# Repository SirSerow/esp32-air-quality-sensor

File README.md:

# ESP32 Air Quality Sensor

ESP32-C6 firmware for reading AHT20 (temperature/humidity) and ENS160 (air quality) data, storing historical samples (SD card preferred, NVS fallback), showing live values on an SSD1306 OLED, and serving a built-in web dashboard over external Wi-Fi when available, with SoftAP fallback.

## Sensor Readings

The device measures six quantities using two sensors on the I²C bus:

| Metric | Sensor | Unit | Good | Moderate | Poor |
|---|---|---|---|---|---|
| Temperature | AHT20 | °C | ≤ 26 | 26 – 30 | > 30 |
| Relative Humidity | AHT20 | % | 30 – 60 | 60 – 70 | > 70 or < 20 |
| eCO₂ | ENS160 | ppm | < 800 | 800 – 2 000 | > 2 000 |
| AQI | ENS160 | 1–5 | 1 – 2 | 3 | 4 – 5 |
| TVOC | ENS160 | ppb | < 220 | 220 – 660 | > 660 |
| ENS Validity | ENS160 | 0–3 | 0 (normal) | 1–2 (warm-up) | 3 (error) |

**AHT20** measures capacitive relative humidity and temperature. Readings are available within seconds of power-on and are unaffected by air quality.

**ENS160** is a metal-oxide gas sensor that estimates eCO₂ and TVOC algorithmically. It requires a warm-up period of ~30 s (validity = 1) and a start-up conditioning phase of ~3 min (validity = 2) before readings are reliable (validity = 0). The eCO₂ value is *not* a direct CO₂ measurement — it is derived from the TVOC signal and correlates with air freshness and human presence. Outdoor air is approximately 400 ppm eCO₂.

## Hardware
- ESP32-C6-DevKitC-1
- Sensor board with:
  - AHT20 temperature/humidity sensor
  - ENS160 air quality sensor

## Current Features
- Reads and logs:
  - Temperature (°C)
  - Humidity (%)
  - AQI
  - TVOC (ppb)
  - eCO2 (ppm)
  - ENS validity flag
- Stores sensor history to SD card (`/sdcard/logs.csv`) when available.
- Falls back to NVS circular buffer storage if SD card is unavailable.
- OLED interface (SSD1306, 128x64, I2C 0x3C):
  - 4-line live status view (time, T/RH, AQI/TVOC, eCO2/validity)
  - Health code markers per value (`G`/`Y`/`R`)
  - Button toggle on GPIO5 (press to turn OLED on/off)
- Tries external Wi-Fi first, then falls back to SoftAP only if STA is unavailable.
- Starts built-in HTTP server automatically on boot.
- Web dashboard at `/` with:
  - Live-updating table of stored values
  - Separate graph for each metric
- JSON API at `/json` for the built-in dashboard recent window.
- CSV download endpoint at `/csv`.
- Versioned server sync API under `/api/v1` for status, time-bounded history, and incremental polling.
- Optional Docker Compose analysis server for Raspberry Pi or another machine:
  - Polls the ESP32 sync API and imports all history on first connection.
  - Stores readings in SQLite.
  - Full-featured web dashboard (see [Web Analysis Dashboard](#web-analysis-dashboard)) with range filters, aggregation views, interactive charts, summary statistics, CSV export, dark mode, and a collapsible sensor reference guide.
- Syncs time over the STA connection when external Wi-Fi is available.
- Starts mDNS on STA so the dashboard can be reached via a stable `.local` name.

## Default Runtime Configuration
- STA dashboard URL: `http://co2-sensor.local/` when `WIFI_STA_SSID` / `WIFI_STA_PASS` are configured and reachable
- mDNS hostname: `co2-sensor`
- mDNS instance name: `CO2 Sensor`
- SoftAP SSID: `CO2-Sensor-AP`
- SoftAP password: `co2sensor123`
- SoftAP fallback URL: `http://192.168.4.1/`
- JSON endpoint: `/json`
- CSV endpoint: `/csv`
- Server status endpoint: `/api/v1/status`
- Server records endpoint: `/api/v1/records`
- Server sync endpoint: `/api/v1/sync`
- Sampling interval: 1 minute (`SENSOR_READ_INTERVAL_MS = 60000`)
- NVS ring-buffer capacity: 180 points (`NVS_SLOT_COUNT = 180`)
- SD log file path: `/sdcard/logs.csv`
- OLED I2C address: `0x3C` (SSD1306)
- OLED toggle button GPIO: `5`

## Project Structure
- `src/` main application code
- `include/` project headers
- `lib/` external/project libraries
- `test/` test files
- `server/` Dockerized data collector and analysis dashboard
- `platformio.ini` PlatformIO configuration
- `CMakeLists.txt` CMake/ESP-IDF project file
- `sdkconfig.esp32-c6-devkitc-1` board-specific ESP-IDF config

## Build, Flash, Monitor
From the project root:

```bash
/home/netlister/.platformio/penv/bin/platformio run -e esp32-c6-devkitc-1
/home/netlister/.platformio/penv/bin/platformio run -e esp32-c6-devkitc-1 -t upload
/home/netlister/.platformio/penv/bin/platformio device monitor -b 115200
```

Use the `~/.platformio/penv/bin/platformio` binary on this machine. `/usr/bin/platformio` resolves to an older incompatible core here.

## Wi-Fi Setup
1. Copy `src/secrets.h.example` to `src/secrets.h` if you have not created it yet.
2. Set `WIFI_STA_SSID` and `WIFI_STA_PASS` to the external Wi-Fi network you want the ESP32 to join.
3. Keep `WIFI_AP_SSID` and `WIFI_AP_PASS` set for fallback access when the external network is unavailable.
4. Rebuild and flash after changing credentials.

## Accessing the Dashboard
1. Power/flash the board and wait for boot logs.
2. If STA connects successfully, open:
   - Dashboard: `http://co2-sensor.local/`
   - JSON: `http://co2-sensor.local/json`
   - CSV: `http://co2-sensor.local/csv`
   - Server API status: `http://co2-sensor.local/api/v1/status`
3. If `.local` resolution is unreliable on your client, use the STA IP address printed in the boot log instead.
4. If STA is unavailable, connect your phone/laptop to Wi-Fi `CO2-Sensor-AP` and use:
   - Dashboard: `http://192.168.4.1/`
   - JSON: `http://192.168.4.1/json`
   - CSV: `http://192.168.4.1/csv`
   - Server API status: `http://192.168.4.1/api/v1/status`

## Network Startup Behavior
1. Boot initializes storage and sensors.
2. Firmware attempts STA connection using `WIFI_STA_SSID` and `WIFI_STA_PASS`.
3. On STA success, the device syncs time with `pool.ntp.org`, starts mDNS, and serves HTTP on the STA interface.
4. On STA failure or when credentials are blank, the device starts the fallback SoftAP and serves HTTP at `192.168.4.1`.

## OLED Display Layout
- Line 1: local time (`YY-MM-DD HH:MM`) when time is synced
- Line 2: temperature and humidity (`T` / `H`)
- Line 3: AQI and TVOC (`A` / `T`)
- Line 4: eCO2 and ENS validity (`C` / `V`)
- Marker legend: `G` = good, `Y` = warning, `R` = bad
- If data is unavailable for a sensor, value fields show `-`

## Data Source Behavior
- Startup tries SD card first (SPI pins: MISO=21, MOSI=22, CLK=19, CS=20).
- If SD mount succeeds, logs are appended to `/sdcard/logs.csv`.
- If SD mount fails, logging continues in NVS (`sensorlog` namespace).
- Web graph/table endpoints read from SD when available, otherwise from NVS.

## Server API
The server-facing API is separate from the dashboard endpoints and is intended for periodic polling by another service.

General behavior:
- All `/api/v1/*` endpoints return JSON.
- Historical results are ordered oldest to newest.
- Records with `unix_time = 0` are excluded from `/api/v1/*`.
- Storage source is reported as `"sd"` or `"nvs"`.

### `GET /api/v1/status`
Returns current device metadata and the newest valid-timestamp record.

Example fields:
- `device_time_unix`
- `sample_interval_sec`
- `storage_source`
- `sd_ready`
- `nvs_ready`
- `latest_record`

### `GET /api/v1/records`
Returns a bounded history window.

Query parameters:
- `from`: optional inclusive unix timestamp
- `to`: optional inclusive unix timestamp
- `limit`: optional number of rows, default `120`, max `240`

Behavior:
- With no `from` and no `to`, returns the newest `limit` records.
- With `from` and/or `to`, returns the matching chronological slice.
- Response includes `count`, `limit`, `has_more`, `source`, `from`, `to`, and `entries`.

Examples:
- Newest 60 rows: `/api/v1/records?limit=60`
- Last day starting at a timestamp: `/api/v1/records?from=1712800000`
- Bounded range: `/api/v1/records?from=1712800000&to=1712886400&limit=120`

### `GET /api/v1/sync`
Returns records newer than a server-held cursor for efficient incremental sync.

Query parameters:
- `since`: optional exclusive unix timestamp cursor, default `0`
- `limit`: optional batch size, default `120`, max `240`

Response fields:
- `count`
- `limit`
- `has_more`
- `next_since`
- `source`
- `entries`

Polling model:
1. Call `/api/v1/sync?since=0` for the initial import.
2. Store the returned `next_since` value after successfully ingesting the batch.
3. If `has_more` is `true`, call `/api/v1/sync?since=<next_since>` again immediately.
4. Otherwise wait until the next polling interval.

## Docker Analysis Server
Run the companion server on a Raspberry Pi or separate machine on the same network:

```bash
SENSOR_BASE_URL=http://192.168.1.50 docker compose up --build -d
```

Open `http://localhost:8000/` on that machine. Replace `192.168.1.50` with the ESP32 STA IP address from the serial boot log. Set `SERVER_PORT=8080` if port 8000 is already in use.

The server persists data in a Docker volume named `co2_sensor_data`. On first successful connection it calls the ESP32 `/api/v1/sync?since=0` endpoint until all available history has been imported, then continues incremental polling using the returned cursor. See `server/README.md` for API details and operational notes.

### Migrating the analysis server to another machine

Use the migration scripts to move the Docker volume that contains the SQLite
database. The export script stops the server briefly so the SQLite database and
WAL files are captured consistently, then restarts it.

On the current machine:

```bash
./scripts/export-server-data.sh
scp backups/co2-sensor-data-*.tgz pi@raspberrypi.local:/home/pi/co2-sensor/
```

On the new Raspberry Pi, from the repository root:

```bash
./scripts/import-server-data-raspberry-pi.sh co2-sensor-data-YYYYMMDDTHHMMSSZ.tgz
curl http://localhost:8000/api/status
```

Set `SENSOR_BASE_URL` in `.env` on the Raspberry Pi to the ESP32 STA IP address
or pass it when starting Compose. A 64-bit Raspberry Pi OS install is
recommended for Docker. The server image uses the official multi-architecture
Python image and avoids optional native Uvicorn extras, so it should build on a
Raspberry Pi without project-specific Docker changes.

## Web Analysis Dashboard

The companion analysis server (`server/`) runs as a Docker container and provides a full-featured dashboard accessible from any browser on the local network.

### Starting the server

```bash
cp .env.example .env          # set SENSOR_BASE_URL to the ESP32 IP or co2-sensor.local
docker compose up -d --build
```

Open `http://<server-ip>:8000/` in any browser.

### Features

**Data range and aggregation**
Select a preset time range (last 24 h / 7 days / 30 days / year / all) or enter a custom start/end date. Choose between raw samples, minute averages, hourly averages, or daily averages.

**Summary cards**
Six cards — one per metric — show the average, minimum, and maximum value for the selected range. Each card has a coloured top bar matching the metric's chart colour.

**Interactive charts**
One chart per metric, laid out in a responsive grid:
- Temperature and Humidity — side by side
- eCO₂ — full-width, taller
- AQI and TVOC — side by side
- ENS Validity — full-width, compact

Every chart features:
- Area gradient fill under the line
- Smart X-axis time labels that switch between `HH:mm`, `HH:mm` with date, or date-only depending on the selected range
- Dashed threshold lines (yellow/red) marking health boundaries
- Lightly shaded danger zones above each threshold
- **Expand button** (`⤢`) in the chart header — click to make any chart full-width and taller; state is saved across page reloads

Hovering over a chart shows a crosshair and a tooltip with the exact timestamp and value at that point.

**Recent rows table**
Collapsible table showing the 80 most recent readings. Air quality cells are colour-coded green / amber / red. Click the header row to collapse or expand.

**Sensor reference guide**
Collapsible section (collapsed by default) with one card per metric explaining what the sensor measures, a good / moderate / poor range table, and practical notes. Useful as a quick in-page reference without needing external documentation.

**Sync controls**
- **Sync** — triggers an immediate incremental poll of the ESP32
- **Full import** — re-imports the entire ESP32 history from timestamp 0

**Settings**
Click the ⚙ button to change the ESP32 address at runtime without restarting the server. The new address takes effect immediately and the sync loop reconnects automatically.

**Dark mode**
Click the ◐ button to toggle between light and dark theme. The preference is saved in `localStorage`.

**CSV export**
Downloads all readings in the selected time range as a plain CSV file.

### Screenshot

## KiCad Schematic & PCB Design
The hardware was designed in KiCad and includes:
- ESP32-C6 module connections (power, boot, and programming signals)
- I2C routing for AHT20 and ENS160 sensors
- GPIO breakout for OLED button and SPI SD card interface
- Compact 2-layer PCB layout optimized for sensor board assembly

### Schematic

### PCB Layout

### 3D PCB Views
Front view:

Back view:

And yes, one design choice may look unnecessary - purely for "airflow optimization," obviously.

## Final Result Photos
Assembled/produced board (front):

Assembled/produced board (back):

## Example Serial Logs
```text
I (...) MAIN: NVS logging enabled (sensorlog)
I (...) MAIN: NVS stats: used=... free=... total=... namespaces=...
I (...) NET: Connecting to external WiFi SSID=...
I (...) NET: STA connected: IP=192.168.1.50 GW=192.168.1.1
I (...) MDNS: mDNS started: http://co2-sensor.local/
I (...) WEB: Web server started on http://co2-sensor.local/
I (...) MAIN: AHT: T=25.17 C  RH=47.53 %
I (...) MAIN: ENS: AQI=3  TVOC=331 ppb  eCO2=812 ppm
```

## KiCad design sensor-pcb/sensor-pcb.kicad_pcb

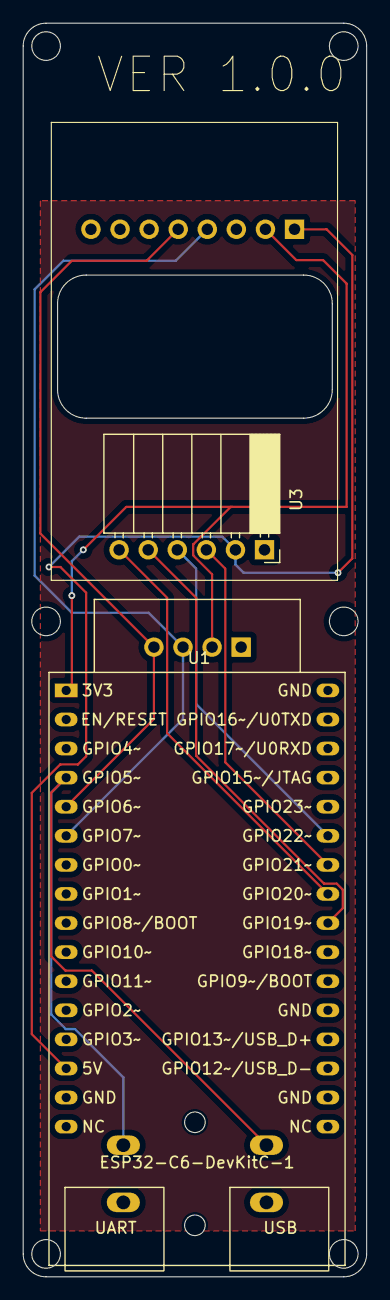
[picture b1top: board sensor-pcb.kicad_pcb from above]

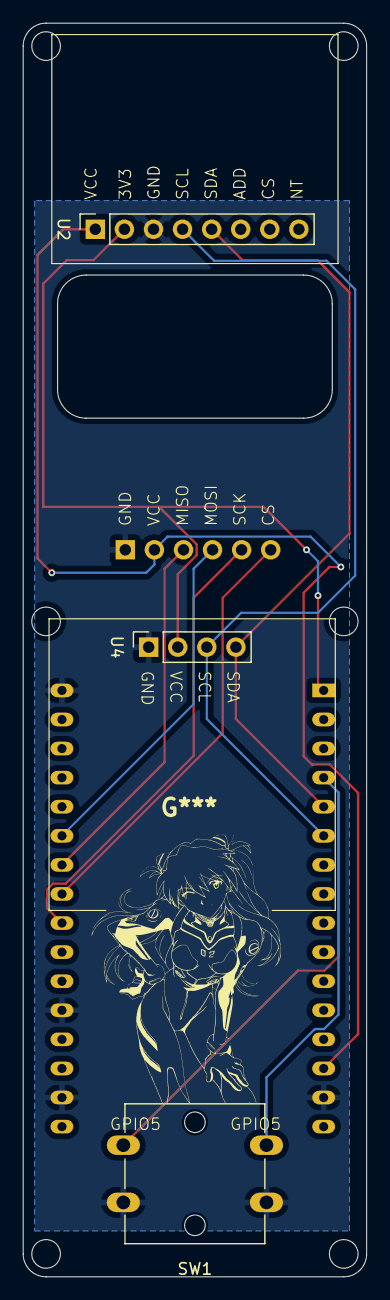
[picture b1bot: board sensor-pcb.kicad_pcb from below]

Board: 2 copper layers, 30.0 x 109.5 mm, 5 parts (3 on the bottom side), 10 nets.

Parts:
SW1: SW_Push_Dual; SW_SPST_Omron_B3F-40xx
U1: ESP32-C6-DevKitC-1
U2: PinSocket_1x08_P2.54mm_Vertical
U3: PinSocket_1x06_P2.54mm_Horizontal
U4: PinSocket_1x04_P2.54mm_Vertical

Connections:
+3.3V: U1.1 (3V3), U2.2 (3V3), U4.2 (VCC)
+5V: U1.14 (5V), U2.1 (VIN), U3.2 (VCC)
CS: U1.25 (GPIO20), U3.6 (CS)
GND: SW1.1, U1.15 (GND), U1.18 (GND), U1.21 (GND), U1.32 (GND), U2.3 (GND), U3.1 (GND), U4.1 (GND)
GPIO5: SW1.2, U1.4 (GPIO5/MTDI)
MISO: U1.26 (GPIO21), U3.3 (MISO)
MOSI: U1.27 (GPIO22), U3.4 (MOSI)
SCK: U1.24 (GPIO19), U3.5 (SCK)
SCL: U1.6 (GPIO7), U2.4 (SCL), U4.3 (SCL)
SDA: U1.5 (GPIO6), U2.5 (SDA), U4.4 (SDA)

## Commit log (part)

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2026-02-11 feat(sensor): added initial code for sensor data readout
2026-02-14 feat(sensor): added wifi hotspot. added webpage.
2026-02-14 feat(sensor): added real time synchronization on startup
2026-02-15 feat(sd): added writing data to the sd card. fixed memory partition in pio.ini
2026-02-15 fix(chart): updated chart data range
2026-02-19 feat(csv): added an endpoint to load csv data file
2026-02-23 feat(pcb): added pcb design files
2026-03-04 feat(oled): added oled and button
2026-03-04 feat(oled): added date and time
2026-03-06 fix(doc): updated readme and added images
2026-04-12 feat(csv): add filtering for current year and optional period in graph generation
2026-04-12 fix(main): ensure proper cleanup of network interface and improve error handling in ENS160 data retrieval
2026-04-12 refactor(main): split single files into sepoarate modules
2026-04-12 feat(web_server): added new endpoints for working with remote server
2026-04-15 feat(network): implement mDNS support for external Wi-Fi connectivity and service discovery
2026-04-16 feat(display): added network information display
2026-04-17 feat(web-server): added web server for reading analysis
2026-04-20 feat(backup): add scripts for exporting and importing server data
